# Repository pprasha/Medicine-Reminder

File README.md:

## This project aims to create a medicine reminder system that utilizes an esp8266 chip in order to remind user to take medication.

# Setup - 
  1. Power on device
  2. Look for "MD123879" in network settings
  3. Use password "$med123789"
  4. Navigate to ip address 192.168.4.22
  5. Follow on screen instructions then click save.

# Prototype -

# Prototype w/ Case - 

# Sample - 

# Computer Interface - 

# Future Consideration -

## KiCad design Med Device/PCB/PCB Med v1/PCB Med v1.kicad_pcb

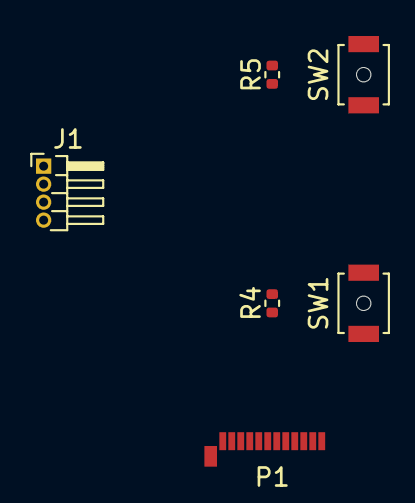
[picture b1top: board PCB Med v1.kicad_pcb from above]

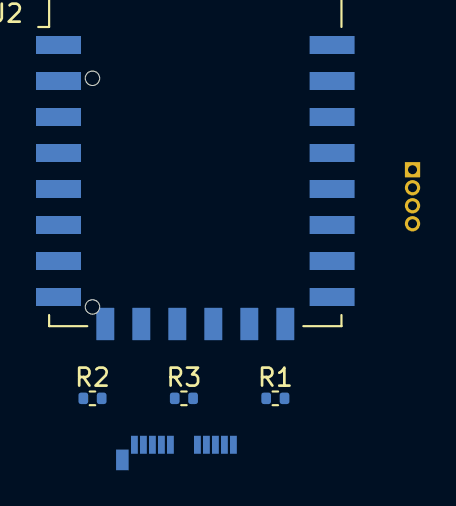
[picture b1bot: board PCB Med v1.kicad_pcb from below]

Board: 2 copper layers, 10 parts (4 on the bottom side), 10 nets, no tracks yet.

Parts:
J1: Conn_01x04_Female; PinHeader_1x04_P1.00mm_Horizontal
P1: USB_C_Plug; USB_C_Plug_Molex_105444
R1, R2, R3, R4, R5: 10K; R_0402_1005Metric
SW1, SW2: SW_MEC_5G; SW_SPST_B3U-1000P-B
U2: ESP-12E

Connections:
GND: J1.1, P1.A1 (GND), P1.A12 (GND), P1.B1 (GND), P1.B12 (GND), R3.2, R4.2, R5.2, U2.15 (GND)
unnamed: J1.2, R1.1, R2.1, SW1.1 (A), SW1.2 (A), SW2.1 (A), SW2.2 (A), U2.8 (VCC)
unnamed: J1.3, U2.20 (GPIO5)
unnamed: J1.4, U2.19 (GPIO4)
unnamed: P1.A4 (VBUS), P1.A9 (VBUS), P1.B4 (VBUS), P1.B9 (VBUS)
unnamed: R1.2, U2.3 (EN)
unnamed: R2.2, U2.18 (GPIO0)
unnamed: R3.1, U2.16 (GPIO15)
unnamed: R4.1, U2.6 (GPIO12)
unnamed: R5.1, U2.7 (GPIO13)

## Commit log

2022-12-25 Create Version 1
2022-12-25 Create Version 2
